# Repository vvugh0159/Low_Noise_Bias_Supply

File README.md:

# Low_Noise_Bias_Supply
KiCad schematic and PCB for 3.3V output bias supply

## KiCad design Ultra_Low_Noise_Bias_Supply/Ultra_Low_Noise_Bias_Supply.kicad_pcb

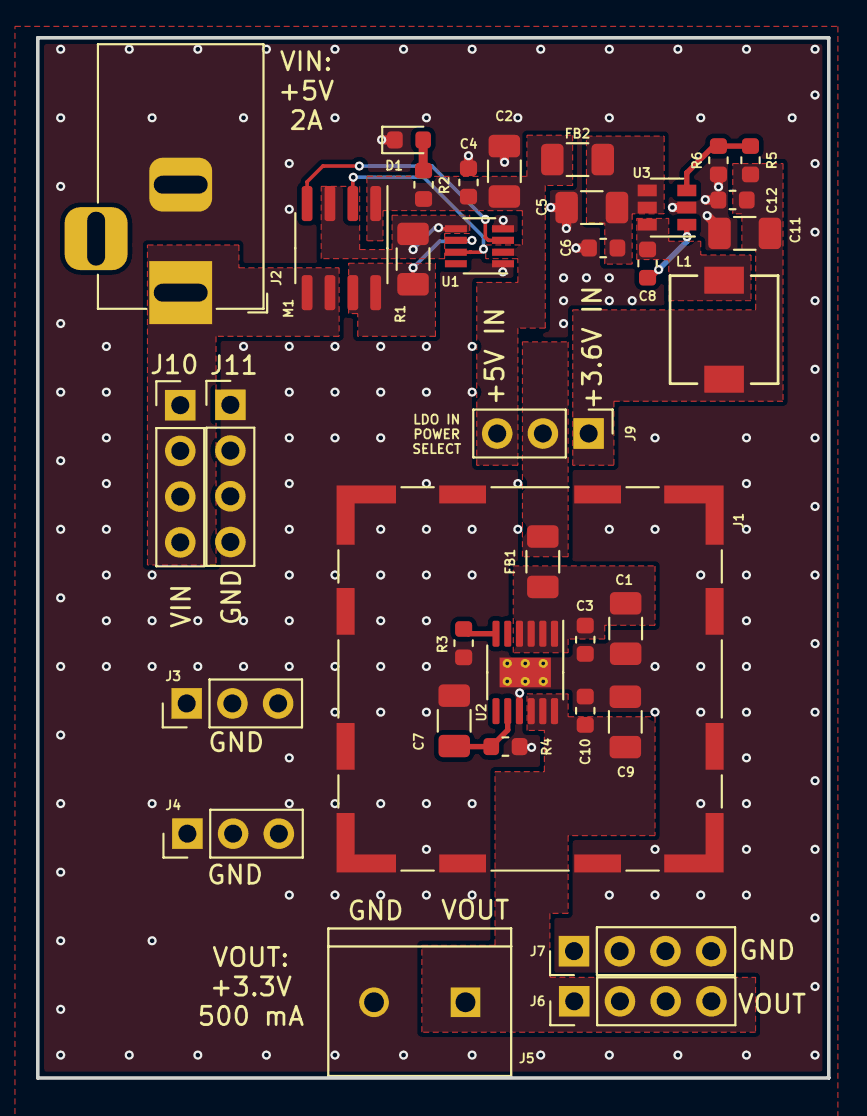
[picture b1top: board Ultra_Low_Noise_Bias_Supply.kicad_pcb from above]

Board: 2 copper layers, 43.9 x 57.8 mm, 36 parts (0 on the bottom side), 18 nets.

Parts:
C1, C2, C5, C7, C9, C11: 10uF; C_1206_3216Metric
C3, C4, C6, C8, C10, C12: 0.1uF; C_0603_1608Metric
D1: LED_ALT; D_0603_1608Metric
FB1, FB2: 74279218; L_1206_3216Metric
J1: 36103205; Wuerth_36103205_20x20mm
J2: Barrel_Jack; BarrelJack_Horizontal
J3, J4, J9: 61300311121; PinHeader_1x03_P2.54mm_Vertical
J5: VAL**; TE_282837-2
J6, J7, J10, J11: 61300411121; PinHeader_1x04_P2.54mm_Vertical
L1: 10uH; Inductor_SMD_6MM_BY_6MM
M1: SI4559ADY-T1-GE3; SOIC-8_3.9x4.9mm_P1.27mm
R1: 25m; R_1206_3216Metric
R2, R3: 300; R_0603_1608Metric
R4: 33k; R_0603_1608Metric
R5: 26.1k; R_0603_1608Metric
R6: 10k; R_0603_1608Metric
U1: LTC4361-2; TSOT-23-8
U2: LT3045; MSOP-12-1EP_3x4mm_P0.65mm_EP1.65x2.85mm_ThermalVias
U3: TPS560430; SOT-23-6

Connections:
+3V3: C9.1, C10.1, J5.1, J6.1, J6.2, J6.3, J6.4, U2.10, U2.11, U2.12
+5V: C2.1, C4.1, FB2.2, J9.3, M1.1, R2.2, U1.2
/+3.6V: C11.1, C12.1, J9.1, L1.1, R5.2
/IN_BUCK: C5.1, C6.1, FB2.1, U3.4, U3.5
/IN_LDO: C1.1, C3.1, FB1.1, U2.1, U2.2, U2.3, U2.4
/VFB_TPS560430: R5.1, R6.2, U3.3
/VIN: J2.1, J10.1, J10.2, J10.3, J10.4, M1.5, M1.6
/VSW_BUCK: C8.2, L1.2, U3.6
GND: C1.2, C2.2, C3.2, C4.2, C5.2, C6.2, C7.2, C9.2, C10.2, C11.2, C12.2, D1.1, J1.1, J2.2, J3.1, J3.2, J3.3, J4.1, J4.2, J4.3, J5.2, J7.1, J7.2, J7.3, J7.4, J11.1, J11.2, J11.3, J11.4, R3.1, R4.1, R6.1, U1.1, U1.4, U2.9, U2.13, U3.2
unnamed: C7.1, R4.2, U2.8
unnamed: C8.1, U3.1
unnamed: D1.2, R2.1
unnamed: FB1.2, J9.2
unnamed: M1.2, U1.7
unnamed: M1.3, R1.1, U1.5
unnamed: M1.4, U1.3
unnamed: M1.7, M1.8, R1.2, U1.6
unnamed: R3.2, U2.6

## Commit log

2020-09-19 First commit of low noise bias supply project
